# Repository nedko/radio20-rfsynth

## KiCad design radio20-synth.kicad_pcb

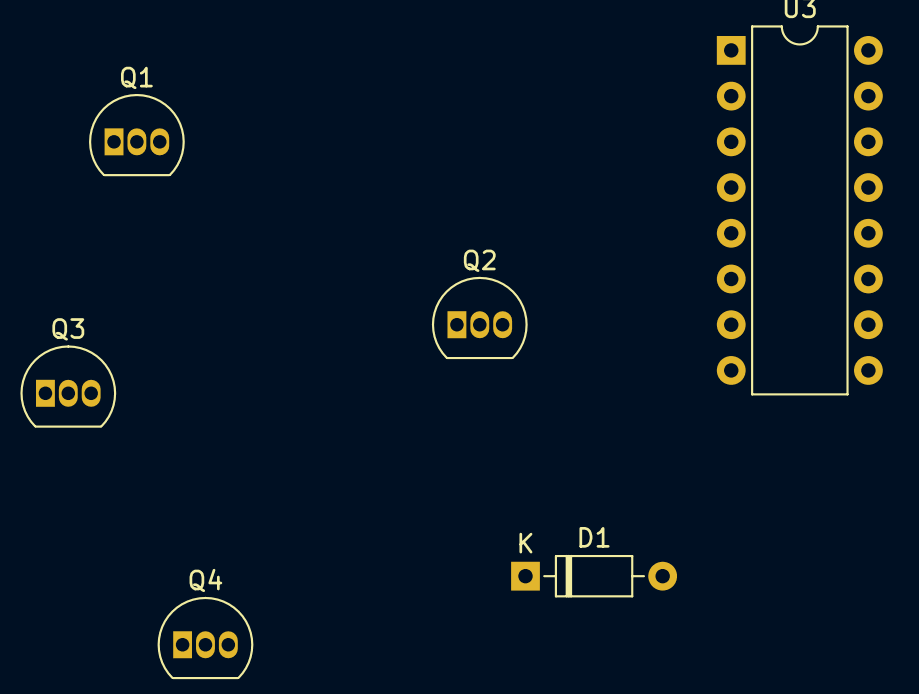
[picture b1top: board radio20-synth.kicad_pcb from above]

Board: 2 copper layers, 6 parts (0 on the bottom side), 7 nets, no tracks yet.

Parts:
D1: КД503А; D_DO-35_SOD27_P7.62mm_Horizontal
Q1, Q2: КТ315Г; TO-92_Inline
Q3: КТ361Г; TO-92_Inline
Q4: КП307Г; TO-92_Inline
U3: К500ЛМ102; DIP-16_W7.62mm

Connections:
GNDD: U3.1 (GND), U3.16 (GND)
unnamed: U3.4, U3.5
unnamed: D1.1 (K), Q1.1 (C), Q3.2 (B)
unnamed: Q1.2 (B), Q2.2 (B)
unnamed: Q2.1 (C), Q3.1 (C)
unnamed: U3.2, U3.6, U3.7
unnamed: U3.3, U3.10, U3.11, U3.12, U3.13

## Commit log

2023-02-14 Import current version from xlrdac commit f4b8108236c429252e63c5fa0e5a4146bb61bf80
2023-02-14 Add a .gitignore file (kicad)
2023-02-14 Add "Синтезатор частоты трансивера; Денисов В. (RA6LM), Ушич В. (UW6LI), Спирин В. (UA6LGY).html"
2023-02-15 A1/sch: adjust title block
2023-02-15 sch: adjust blocks; add freq table
2023-02-15 sch: Fix typo in freq table; adjust formatting
2023-02-15 A2: Adjust for ladihw symbols; fix voltages
    Use ladihw library
    Fix voltages:
    * -5.2V (ECL) is now used instead of -5V
    * 24V is now used instead of 12V
2023-02-15 Add ladihw-kicad-symbols git subproject
2023-02-15 use ladihw (kicad-symbols) from submodule
2023-02-15 add schematic pdf renderings
2023-03-20 Update to kicad7; flush WIP
2023-03-20 Add kicad-symbols-GOST-2.728 submodule
2023-03-20 sym-lib-table: add GOST-2.728.kicad_sym from submodule
2023-03-20 Flush WIP
